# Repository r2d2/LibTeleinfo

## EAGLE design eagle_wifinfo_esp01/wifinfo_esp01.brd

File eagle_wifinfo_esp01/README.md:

# ESP01 support

This directory contains eagle schematics for LibTeleinfo on ESP01.

ESP01 is very cheap (a couple of dollars).
But the serial link seems to be less reliable (I often had read errors).
Code has been reworked to validate electrical counter serial input based on known tokens/keywords.

A simple schematics like the one proposed below is doing well the job.

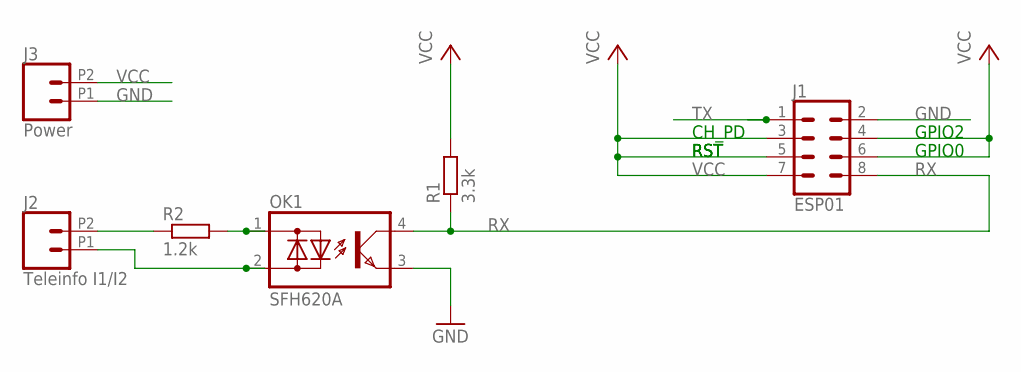
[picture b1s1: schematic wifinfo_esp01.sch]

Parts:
J1: ESP01; 2X4
J2: Teleinfo I1/I2; 1X02_2.54_SCREWTERM
J3: Power; 1X02_2.54_SCREWTERM
OK1: SFH620A; DIL04
R1: 3.3k; 0204/7
R2: 1.2k; 0204/7

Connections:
GND: J1.2, J3.P1 (1), OK1.3 (E)
unnamed: OK1.1 (AC1), R2.2
unnamed: J2.P1 (1), OK1.2 (AC2)
unnamed: J2.P2 (2), R2.1
RX: J1.8, OK1.4 (C), R1.1
TX: J1.1
VCC: J1.3, J1.4, J1.5, J1.6, J1.7, J3.P2 (2), R1.2

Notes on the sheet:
CH_PD
RST
GPIO2
GPIO0

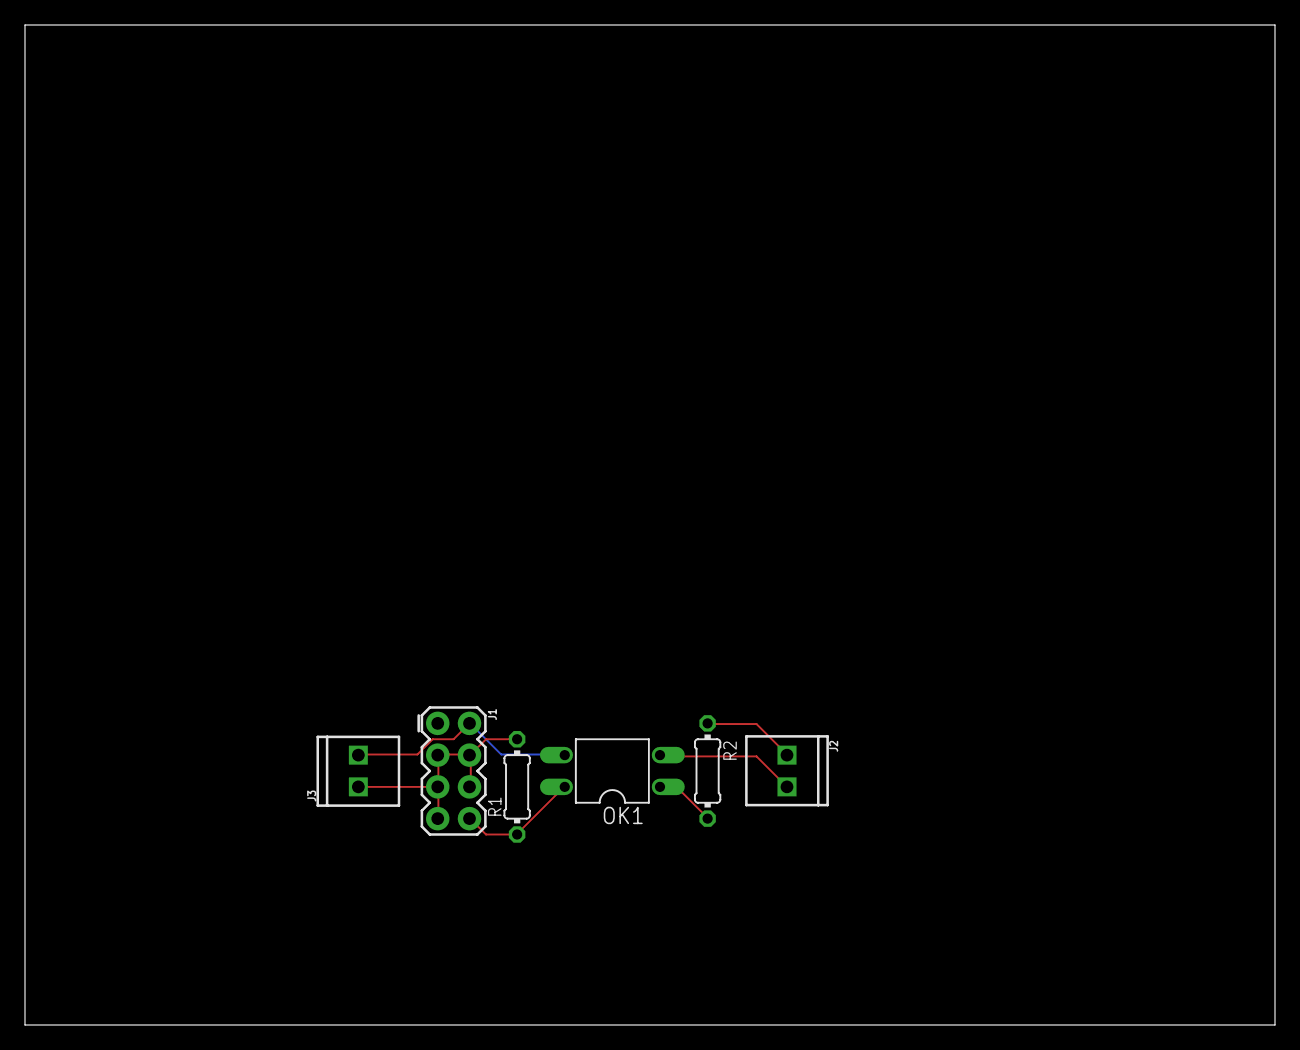
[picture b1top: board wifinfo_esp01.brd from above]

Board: 2 copper layers, 100.0 x 80.0 mm, 6 parts (0 on the bottom side), 6 nets.

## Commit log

2017-11-17 Added a ESP01 define : avoid using leds that do not exist on the ESP01
2017-11-17 *Add a token verification function. On the ESP01 + hardware setup, we often have read errors. A workaround is to verify received tokens against a list of known token. That prevents bad values to be s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
2018-03-02 Adding ESP0 support files & README
2018-03-02 correcting image link for ESP01 support schematics
2018-04-08 Removing DEBUG, ESP01 does not have a spare serial
2018-04-09 ESP01 only has 1 serial port. Correcting temporarly the init code

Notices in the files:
parts and their libraries:
SparkFun-Connectors: Licensing: Creative Commons ShareAlike 4.0 International - https://creativecommons.org/licenses/by-sa/4.0
